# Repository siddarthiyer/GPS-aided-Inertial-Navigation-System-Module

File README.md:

# GPS-aided Inertial Navigation System Module (In Progress)

* MCU: STM32F103C8T6
* Communication Protocol: CAN
* Features: Pitch, Roll, Yaw, Direction, Latitude, Longitude, Temperature, Altitude, Pressure 

<hr>

<h3>CAN Frame </h3>
(Based on CANopen)

Upper 6 bits - Module ID - max 0x3F </br>
Lower 5 bits - Command ID - max 0x1F</br>
CAN ID = (Module ID << 5) | Command ID</br>
Default Module ID : 0x200 (Standard)

| CMD_ID | Name | Sender  | Signals | Start byte | Signal Type | Bits |
| ------ | -----| -------- | --------  | -------- | -------- |-------- |
| `0x001`   | Heartbeat | Module  | Latitude, Longitude  | 0, 4  | IEEE 754 Float, IEEE 754 Float | 32, 32 |

<hr>

<h3>Sensors: </h3>

* MPU-9250
  * 9-axis MEMS sensor
  * Pinout:
    - PB11: SDA
    - PB10: SCL
  * Communication Protocol: I2C
  
* NEO-6M
  * GPS Module
  * Pinout:
    - PA3: TX
    - PA2: RX
  * Communication Protocol: UART
 
* BMP180
  * Barometric Pressure/Temperature/Altitude Sensor
  * Pinout:
    - PB7: SDA
    - PB6: SCL
  * Communication Protocol: I2C

<hr>

<h3>PCB Design </h3>

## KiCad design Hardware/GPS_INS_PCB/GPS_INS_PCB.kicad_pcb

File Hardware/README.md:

# GPS-aided Inertial Navigation System PCB

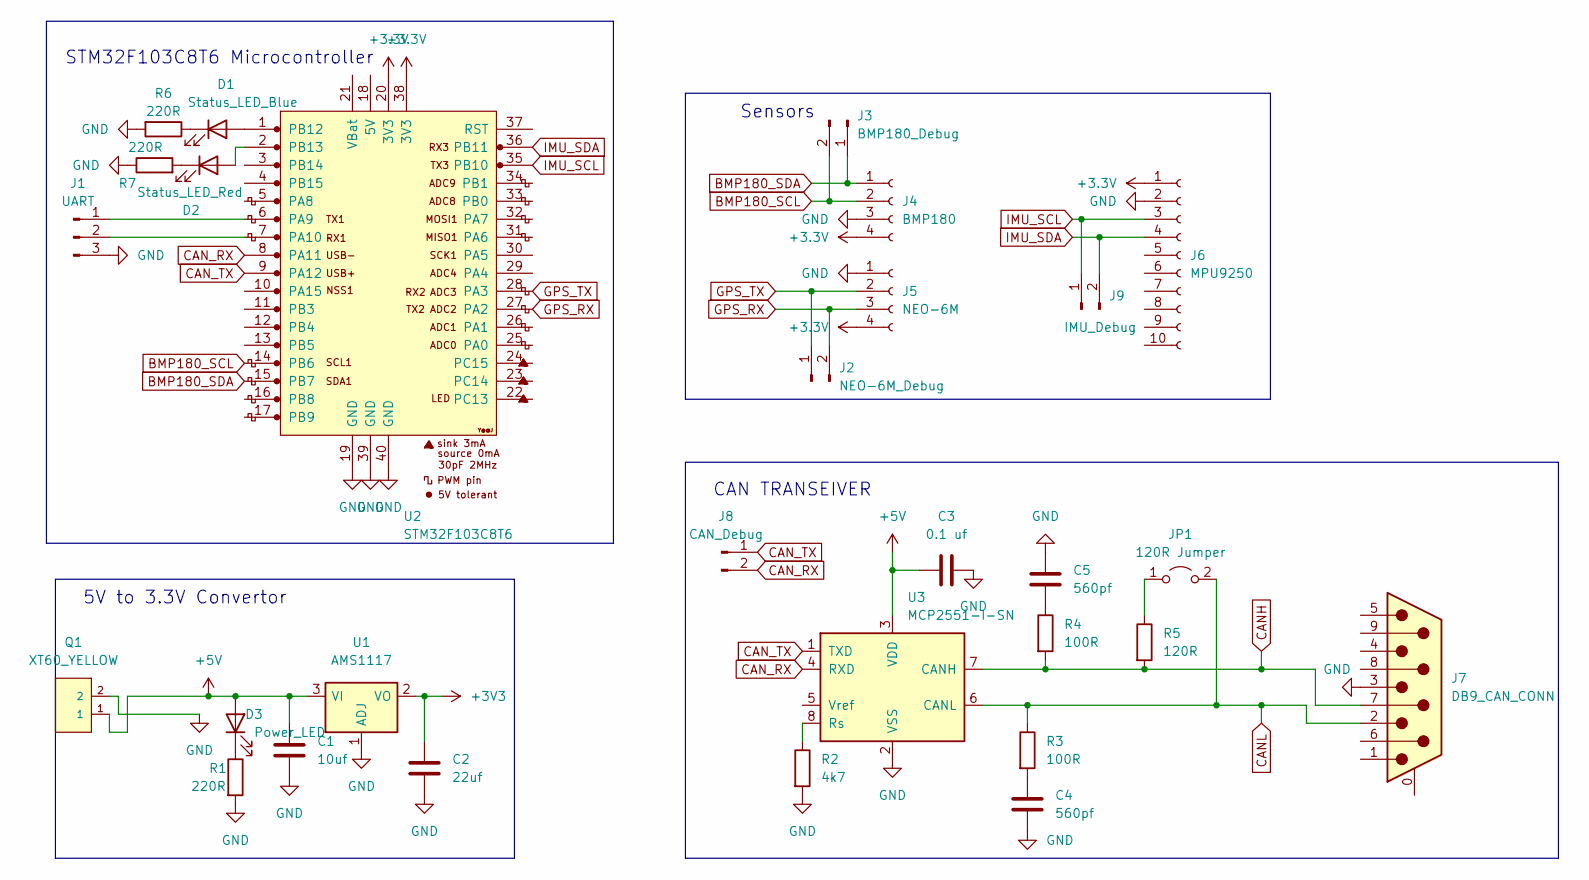
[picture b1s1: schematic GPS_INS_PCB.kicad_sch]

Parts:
C1: 10uf; C_0805_2012Metric_Pad1.18x1.45mm_HandSolder
C2: 22uf; CP_EIA-1608-08_AVX-J_Pad1.25x1.05mm_HandSolder
C3: 0.1 uf; C_0805_2012Metric_Pad1.18x1.45mm_HandSolder
C4, C5: 560pf; C_0805_2012Metric_Pad1.18x1.45mm_HandSolder
D1: Status_LED_Blue; LED_D5.0mm
D2: Status_LED_Red; LED_D5.0mm
D3: Power_LED; LED_D5.0mm
J1: UART; PinHeader_1x03_P2.54mm_Vertical
J2: NEO-6M_Debug; PinHeader_1x02_P2.54mm_Vertical
J3: BMP180_Debug; PinHeader_1x02_P2.54mm_Vertical
J4: BMP180; PinSocket_1x04_P2.54mm_Vertical
J5: NEO-6M; PinSocket_1x04_P2.54mm_Vertical
J6: MPU9250; PinSocket_1x10_P2.54mm_Vertical
J7: DB9_CAN_CONN; DSUB-9_Male_Horizontal_P2.77x2.84mm_EdgePinOffset4.94mm_Hou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
J8: CAN_Debug; PinHeader_1x02_P2.54mm_Vertical
J9: IMU_Debug; PinHeader_1x02_P2.54mm_Vertical
JP1: 120R Jumper; PinHeader_1x02_P2.54mm_Vertical
Q1: XT60_YELLOW; AMASS_XT60PB-M; PARTREV 1.2
R1, R6, R7: 220R; R_0805_2012Metric_Pad1.20x1.40mm_HandSolder
R2: 4k7; R_0805_2012Metric_Pad1.20x1.40mm_HandSolder
R3, R4: 100R; R_0805_2012Metric_Pad1.20x1.40mm_HandSolder
R5: 120R; R_0805_2012Metric_Pad1.20x1.40mm_HandSolder
U1: AMS1117; SOT-223-3_TabPin2
U2: STM32F103C8T6; YAAJ_BluePill_1
U3: MCP2551-I-SN; SOIC-8_3.9x4.9mm_P1.27mm

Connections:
+5V: C1.1, C3.1, D3.2 (A), Q1.1, U1.3 (VI), U3.3 (VDD)
BMP180_SCL: J3.2, J4.2, U2.14 (PB6)
BMP180_SDA: J3.1, J4.1, U2.15 (PB7)
CANH: J7.7, R4.2, R5.2, U3.7 (CANH)
CANL: J7.2, JP1.2 (B), R3.1, U3.6 (CANL); also elsewhere on the board
CAN_RX: J8.2, U2.8 (PA11), U3.4 (RXD)
CAN_TX: J8.1, U2.9 (PA12), U3.1 (TXD)
GND: C1.2, C2.2, C3.2, C4.2, C5.1, J1.3, J4.3, J5.1, J6.2, J7.3, Q1.2, R1.2, R2.2, R6.2, R7.1, U1.1 (ADJ), U2.19 (GND), U2.39 (GND), U2.40 (GND), U3.2 (VSS)
GPS_RX: J2.2, J5.3, U2.27 (PA2)
GPS_TX: J2.1, J5.2, U2.28 (PA3)
IMU_SCL: J6.3, J9.1, U2.35 (PB10)
IMU_SDA: J6.4, J9.2, U2.36 (PB11)
unnamed: C4.1, R3.2
unnamed: C5.2, R4.1
unnamed: D1.1 (K), R6.1
unnamed: D2.1 (K), R7.2
unnamed: D3.1 (K), R1.1
unnamed: J1.1, U2.6 (PA9)
unnamed: J1.2, U2.7 (PA10)
unnamed 19: JP1.1 (A), R5.1; also elsewhere on the board
unnamed: R2.1, U3.8 (Rs)
unnamed: D1.2 (A), U2.1 (PB12)
unnamed: D2.2 (A), U2.2 (PB13)

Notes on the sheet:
5V to 3.3V Convertor
Sensors
CAN TRANSEIVER
STM32F103C8T6 Microcontroller

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
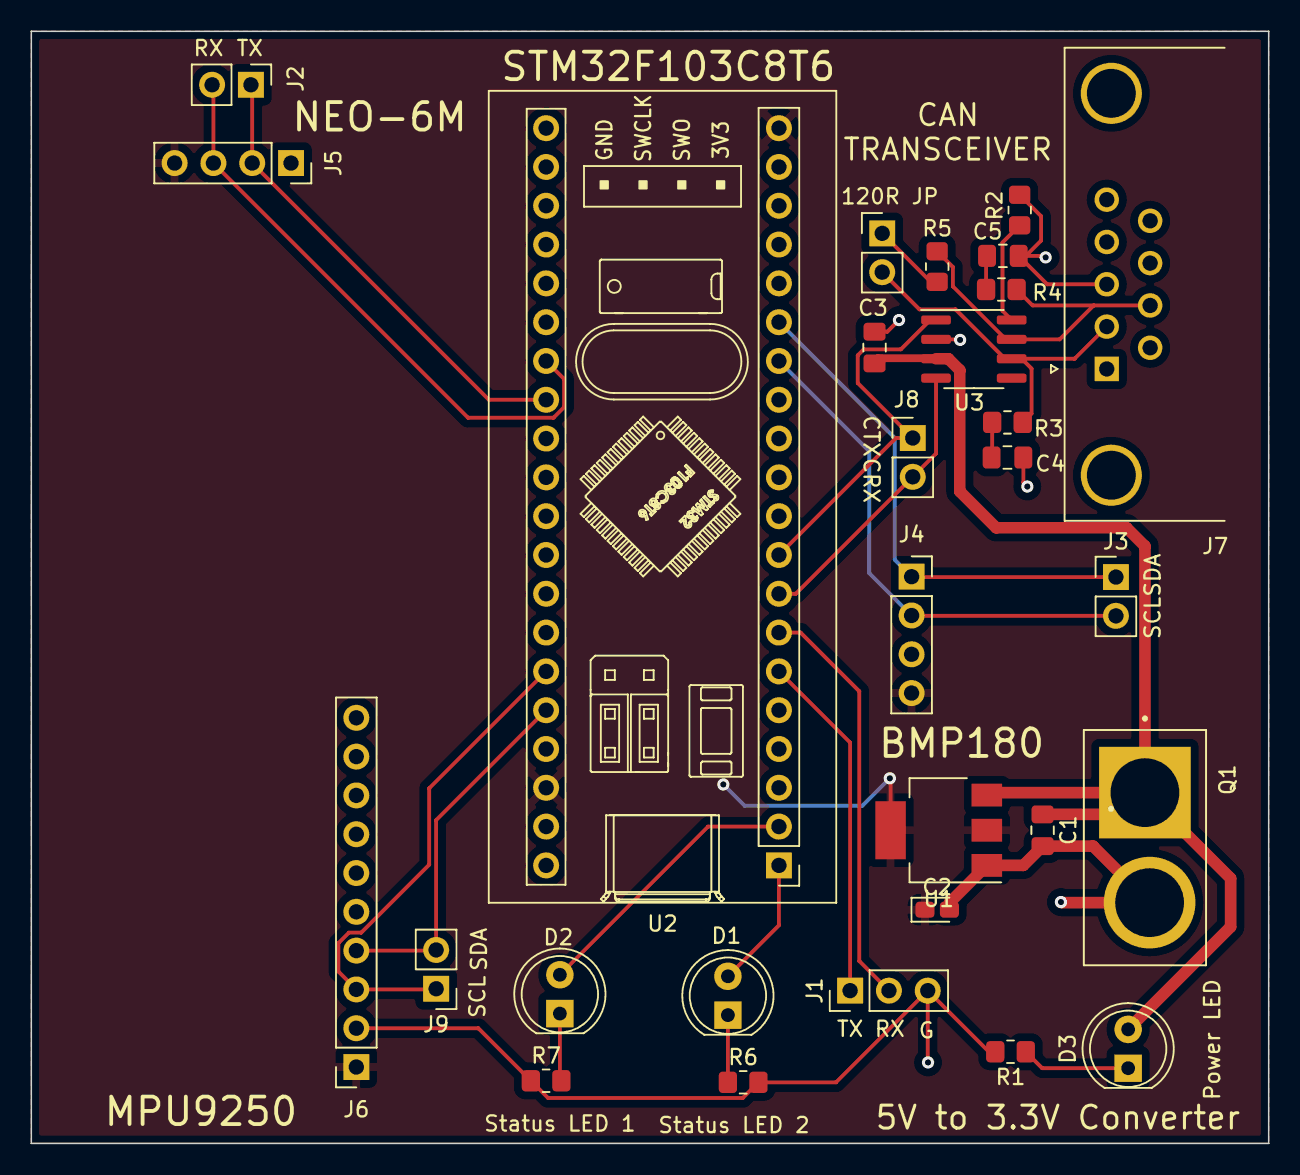
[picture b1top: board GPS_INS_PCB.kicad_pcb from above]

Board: 2 copper layers, 81.0 x 72.8 mm, 29 parts (0 on the bottom side), 24 nets.

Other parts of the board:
120R JP: 120R Jumper; PinHeader_1x02_P2.54mm_Vertical

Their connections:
CANL: 120R JP.2 (B); also elsewhere on the board
unnamed 19: 120R JP.1 (A); also elsewhere on the board

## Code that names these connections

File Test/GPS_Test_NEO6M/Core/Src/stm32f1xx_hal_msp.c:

/* USER CODE BEGIN Header */
/**
  ******************************************************************************
  * @file         stm32f1xx_hal_msp.c
  * @brief        This file provides code for the MSP Initialization
  *               and de-Initialization codes.
  ******************************************************************************
  * @attention
  *
  * Copyright (c) 2022 STMicroelectronics.
  * All rights reserved.
  *
  * This software is licensed under terms that can be found in the LICENSE file
  * in the root directory of this software component.
  * If no LICENSE file comes with this software, it is provided AS-IS.
  *
  ******************************************************************************
  */
/* USER CODE END Header */

/* Includes ------------------------------------------------------------------*/
#include "main.h"
/* USER CODE BEGIN Includes */

/* USER CODE END Includes */

/* Private typedef -----------------------------------------------------------*/
/* USER CODE BEGIN TD */

/* USER CODE END TD */

/* Private define ------------------------------------------------------------*/
/* USER CODE BEGIN Define */

/* USER CODE END Define */

/* Private macro -------------------------------------------------------------*/
/* USER CODE BEGIN Macro */

/* USER CODE END Macro */

/* Private variables ---------------------------------------------------------*/
/* USER CODE BEGIN PV */

/* USER CODE END PV */

/* Private function prototypes -----------------------------------------------*/
/* USER CODE BEGIN PFP */

/* USER CODE END PFP */

/* External functions --------------------------------------------------------*/
/* USER CODE BEGIN ExternalFunctions */

/* USER CODE END ExternalFunctions */

/* USER CODE BEGIN 0 */

/* USER CODE END 0 */
/**
  * Initializes the Global MSP.
  */
void HAL_MspInit(void)
{
  /* USER CODE BEGIN MspInit 0 */

  /* USER CODE END MspInit 0 */

  __HAL_RCC_AFIO_CLK_ENABLE();
  __HAL_RCC_PWR_CLK_ENABLE();

  /* System interrupt init*/

  /** NOJTAG: JTAG-DP Disabled and SW-DP Enabled
  */
  __HAL_AFIO_REMAP_SWJ_NOJTAG();

  /* USER CODE BEGIN MspInit 1 */

  /* USER CODE END MspInit 1 */
}

/**
* @brief UART MSP Initialization
* This function configures the hardware resources used in this example
* @param huart: UART handle pointer
* @retval None
*/
void HAL_UART_MspInit(UART_HandleTypeDef* huart)
{
  GPIO_InitTypeDef GPIO_InitStruct = {0};
  if(huart->Instance==USART1)
  {
  /* USER CODE BEGIN USART1_MspInit 0 */

  /* USER CODE END USART1_MspInit 0 */
    /* Peripheral clock enable */
    __HAL_RCC_USART1_CLK_ENABLE();

    __HAL_RCC_GPIOA_CLK_ENABLE();
    /**USART1 GPIO Configuration
    PA9     ------> USART1_TX
    PA10     ------> USART1_RX
    */
    GPIO_InitStruct.Pin = GPIO_PIN_9;
    GPIO_InitStruct.Mode = GPIO_MODE_AF_PP;
    GPIO_InitStruct.Speed = GPIO_SPEED_FREQ_HIGH;
    HAL_GPIO_Init(GPIOA, &GPIO_InitStruct);

    GPIO_InitStruct.Pin = GPIO_PIN_10;
    GPIO_InitStruct.Mode = GPIO_MODE_INPUT;
    GPIO_InitStruct.Pull = GPIO_NOPULL;
    HAL_GPIO_Init(GPIOA, &GPIO_InitStruct);

  /* USER CODE BEGIN USART1_MspInit 1 */

  /* USER CODE END USART1_MspInit 1 */
  }
  else if(huart->Instance==USART2)
  {
  /* USER CODE BEGIN USART2_MspInit 0 */

  /* USER CODE END USART2_MspInit 0 */
    /* Peripheral clock enable */
    __HAL_RCC_USART2_CLK_ENABLE();

    __HAL_RCC_GPIOA_CLK_ENABLE();
    /**USART2 GPIO Configuration
    PA2     ------> USART2_TX
    PA3     ------> USART2_RX
    */
    GPIO_InitStruct.Pin = GPIO_PIN_2;
    GPIO_InitStruct.Mode = GPIO_MODE_AF_PP;
    GPIO_InitStruct.Speed = GPIO_SPEED_FREQ_HIGH;
    HAL_GPIO_Init(GPIOA, &GPIO_InitStruct);

    GPIO_InitStruct.Pin = GPIO_PIN_3;
    GPIO_InitStruct.Mode = GPIO_MODE_INPUT;
    GPIO_InitStruct.Pull = GPIO_NOPULL;
    HAL_GPIO_Init(GPIOA, &GPIO_InitStruct);

  /* USER CODE BEGIN USART2_MspInit 1 */

  /* USER CODE END USART2_MspInit 1 */
  }

}

/**
* @brief UART MSP De-Initialization
* This function freeze the hardware resources used in this example
* @param huart: UART handle pointer
* @retval None
*/
void HAL_UART_MspDeInit(UART_HandleTypeDef* huart)
{
  if(huart->Instance==USART1)
  {
  /* USER CODE BEGIN USART1_MspDeInit 0 */

  /* USER CODE END USART1_MspDeInit 0 */
    /* Peripheral clock disable */
    __HAL_RCC_USART1_CLK_DISABLE();

    /**USART1 GPIO Configuration
    PA9     ------> USART1_TX
    PA10     ------> USART1_RX
    */
    HAL_GPIO_DeInit(GPIOA, GPIO_PIN_9|GPIO_PIN_10);

  /* USER CODE BEGIN USART1_MspDeInit 1 */

  /* USER CODE END USART1_MspDeInit 1 */
  }
  else if(huart->Instance==USART2)
  {
  /* USER CODE BEGIN USART2_MspDeInit 0 */

  /* USER CODE END USART2_MspDeInit 0 */
    /* Peripheral clock disable */
    __HAL_RCC_USART2_CLK_DISABLE();

    /**USART2 GPIO Configuration
    PA2     ------> USART2_TX
    PA3     ------> USART2_RX
    */
    HAL_GPIO_DeInit(GPIOA, GPIO_PIN_2|GPIO_PIN_3);

  /* USER CODE BEGIN USART2_MspDeInit 1 */

  /* USER CODE END USART2_MspDeInit 1 */
  }

}

/* USER CODE BEGIN 1 */

/* USER CODE END 1 */

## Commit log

2022-07-13 Update BMP180
2022-07-18 PCB Commit
